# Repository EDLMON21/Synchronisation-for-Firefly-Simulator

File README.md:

## 🔥 Project Overview – *Synchronization for Firefly Simulator*  
### 🧠 Team Number: MON-21

👥 **Team Members:**  
- Mohammad Sami  
- Shivam Panwar  
- Gogineni Venkat Sumanth  
- Juluva Yashwanth  
- Lokesh  

---

### 📌 Problem Statement & Solution

Synchronization is a fundamental phenomenon in complex systems 🌐. To study it in real-time with flexibility, we need a programmable system with tunable parameters.

🧾 **Limitations of Old Designs:**  
The classical 1993 electronic fireflies lacked programmability and flexibility.  

⚙️ **Modern Solution:**  
Thanks to advancements in microcontrollers, we now have digital control and customizable experimentation possibilities.

---

### 🔧 Prototyping Journey

**🧩 Initial Prototype:**  
We designed a basic STM32 board with just the microcontroller to gain hands-on experience with PCB design using **STM32G030K8T6**.

**🔁 Second Iteration:**  
Integrated IR LEDs, photodiodes, and supporting components onto the board. Fabricated 2-3 units to test functionality, sync accuracy & design refinements.

**✅ Final Prototype:**  
After validation, we manufactured **9 boards (3×3 matrix)** for full-scale synchronization testing.

💻 Throughout, software development and debugging ran parallel to hardware iterations for smooth integration.

🧑‍🏫 The **STM32G030X** was suggested by our professor due to its suitability.  
🔦 The IR LED & photodiode combo was chosen for ambient light resistance and reliability in synchronization.

---

### ⚙️ Component Choices

- **🔲 STM32G030K8T6**  
  → Chosen from STM32G030 series (as fixed by prof) due to sufficient specs, easy soldering & availability.

- **🔦 IR LED & Phototransistor Pair**  
  → *SFH 4550 & SFH 309 FA*  
  → IR avoids visible light interference. The photodiode has peak sensitivity near **850nm** (matching our IR LED) and a narrow FOV for accurate detection.

- **🧰 Other Components**  
  → Transistors, LDO, micro USB connectors – sourced from WEL stock.

---

### 🚀 Running the Application

1. **🎯 Microcontroller:**  
   - STM32G030K8T6 or STM32G030K6T6  

2. **🛠 IDE:**  
   - STM32CubeIDE  

3. **📥 Compilation & Upload Steps:**  
   - Install **STM32CubeIDE**  
   - Download the `final.ioc` file from the **STM32G030K8T6** folder inside `src`  
   - Load `.ioc` file in your IDE  
   - Save the file to auto-generate code  
   - Replace the generated `main.c` with the `main.c` from the same folder  
   - Build the project 🏗️  
   - Flash the code using **StLink V2** (or equivalent)  
   - 🎉 Synchronization begins once phototransistors start detecting LED flashes!

---

Final Product

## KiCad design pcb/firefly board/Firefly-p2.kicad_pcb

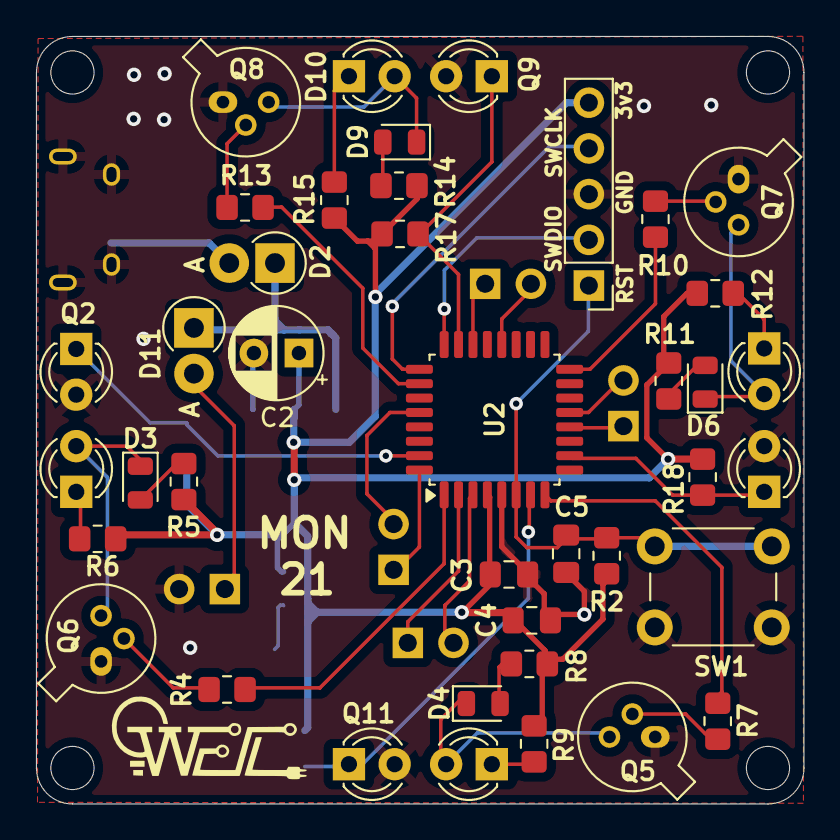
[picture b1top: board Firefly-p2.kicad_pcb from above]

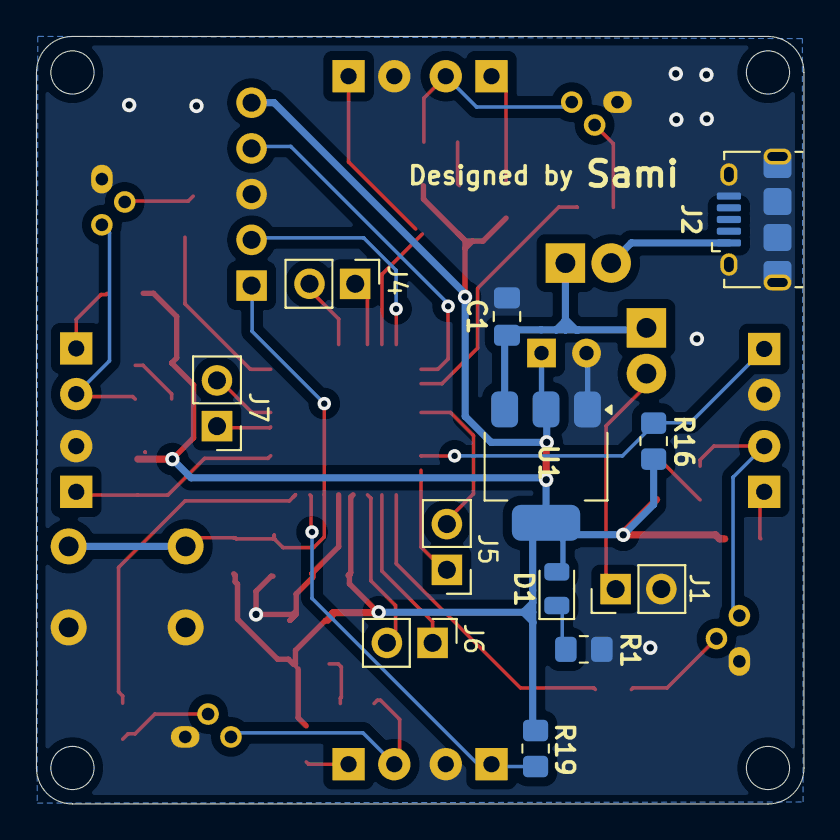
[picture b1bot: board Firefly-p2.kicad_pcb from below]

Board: 2 copper layers, 42.6 x 42.6 mm, 52 parts (12 on the bottom side), 41 nets.

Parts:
C1: 22u; C_0805_2012Metric_Pad1.18x1.45mm_HandSolder
C2: 22uF; CP_Radial_D5.0mm_P2.50mm
C3: 100nF; C_0805_2012Metric_Pad1.18x1.45mm_HandSolder
C4: 10uF; C_0805_2012Metric_Pad1.18x1.45mm_HandSolder
C5: 100n; C_0805_2012Metric_Pad1.18x1.45mm_HandSolder
D1, D3, D4, D6, D9: LED; LED_0805_2012Metric
D2, D11: D_Schottky; D_DO-41_SOD81_P2.54mm_Vertical_AnodeUp
D5, D7, D8, D10: SFH_4550; LED_D3.0mm_Clear
J1: Power_line; PinHeader_1x02_P2.54mm_Vertical
J2: USB_B_Micro; USB_Micro-B_Amphenol_10118194-0001LF_Horizontal
J3: Conn_01x05_Socket; PinHeader_1x05_P2.54mm_Vertical
J4: line_2; PinHeader_1x02_P2.54mm_Vertical
J5: line_3; PinHeader_1x02_P2.54mm_Vertical
J6: line_4; PinHeader_1x02_P2.54mm_Vertical
J7: line_1; PinHeader_1x02_P2.54mm_Vertical
Q2, Q9, Q10, Q11: SFH309; LED_D3.0mm_Clear
Q5, Q6, Q7, Q8: 2N2222; TO-18-3
R1, R4, R7, R10, R13: 1k; R_0805_2012Metric_Pad1.20x1.40mm_HandSolder
R2, R16, R17, R18, R19: 10k; R_0805_2012Metric_Pad1.20x1.40mm_HandSolder
R5, R8, R11, R14: 100r; R_0805_2012Metric_Pad1.20x1.40mm_HandSolder
R6, R9, R12, R15: 330r; R_0805_2012Metric_Pad1.20x1.40mm_HandSolder
SW1: SW_Push; SW_PUSH_6mm
U1: AMS1117-3.3; SOT-223-3_TabPin2
U2: STM32G030K8Tx; LQFP-32_7x7mm_P0.8mm

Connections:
+3.3V: C2.1, C3.1, C4.1, D1.2 (A), J3.5, R2.2, R5.1, R6.1, R8.1, R9.1, R11.1, R12.1, R14.1, R15.1, R16.2, R17.2, R18.2, R19.2, U1.2 (VO), U2.4 (VDD)
/PA0: Q11.1 (C), R19.1, U2.7 (PA0)
/PA1: R7.2, U2.8 (PA1)
/PA3: Q10.1 (C), R18.1, U2.10 (PA3)
/PA5: J7.1, U2.12 (PA5)
/PA6: J7.2, U2.13 (PA6)
/PA11: J4.1, U2.22 (PA9/PA11)
/PA12: Q9.1 (C), R17.1, U2.23 (PA10/PA12)
/PA15: R13.2, U2.26 (PA15)
/PB1: R10.2, U2.16 (PB1)
/PB4: J5.2, U2.28 (PB4)
/PB7: Q2.1 (C), R16.1, U2.31 (PB7)
/PB8: J5.1, U2.32 (PB8)
/PB9: R4.2, U2.1 (PB9)
/PC6: J4.2, U2.20 (PC6)
/PC14: J6.1, U2.2 (PC14)
/PC15: J6.2, U2.3 (PC15)
/RST: C5.1, J3.1, R2.1, SW1.2, U2.6 (NRST)
/SWCLK: J3.4, U2.25 (PA14)
/SWDIO: J3.2, U2.24 (PA13)
GND: C1.2, C2.2, C3.2, C4.2, C5.2, J1.2, J2.5 (GND), J2.6 (Shield), J3.3, Q2.2 (E), Q5.1 (E), Q6.1 (E), Q7.1 (E), Q8.1 (E), Q9.2 (E), Q10.2 (E), Q11.2 (E), R1.2, SW1.1, U1.1 (GND), U2.5 (VSS)
unnamed: D1.1 (K), R1.1
unnamed: D2.2 (A), J2.1 (VBUS)
unnamed: D3.2 (A), R5.2
unnamed: D3.1 (K), D5.2, Q6.3 (C)
unnamed: D4.2 (A), R8.2
unnamed: D4.1 (K), D8.2, Q5.3 (C)
unnamed: D5.1, R6.2
unnamed: D6.2 (A), R11.2
unnamed: D6.1 (K), D7.2, Q7.3 (C)
unnamed: D7.1, R12.2
unnamed: D8.1, R9.2
unnamed: D9.2 (A), R14.2
unnamed: D9.1 (K), D10.2, Q8.3 (C)
unnamed: D10.1, R15.2
unnamed: D11.2 (A), J1.1
unnamed: Q5.2 (B), R7.1
unnamed: Q6.2 (B), R4.1
unnamed: Q7.2 (B), R10.1
unnamed: Q8.2 (B), R13.1
VBUS: C1.1, D2.1 (K), D11.1 (K), U1.3 (VI)

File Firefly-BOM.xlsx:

Name | Qty | Value | Footprint | Type | Supplier | Cost (Rs.)
Capacitor | 1 | 22uF | Capacitor_SMD:C_0805_2012Metric_Pad1.18x1.45mm_HandSolder | Consumable | WEL | NA
Tantalum Capacitor | 1 | 22uF | Capacitor_THT:CP_Radial_D4.0mm_P1.50mm | Consumable | Robu (https://robu.in/product/22uf-16v-tantalum-capacitor-dip-pack-of-5/) | 99/-
Capacitor | 2 | 100nF | Capacitor_SMD:C_0805_2012Metric_Pad1.18x1.45mm_HandSolder | Consumable | WEL | NA
Capacitor | 1 | 10uF | Capacitor_SMD:C_0805_2012Metric_Pad1.18x1.45mm_HandSolder | Consumable | WEL | NA
LEDs | 5 | LED | LED_SMD:LED_0805_2012Metric | Consumable | WEL | NA
Schottky Diode | 2 | D_Schottky | Diode_THT:D_DO-41_SOD81_P2.54mm_Vertical_AnodeUp | Consumable | Robu (https://robu.in/product/1n5817-multicomp-pro-1n5817-schottky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 | 9/-
IR Led | 4 | SFH_4550 | LED_THT:LED_D3.0mm_Clear | Consumable | RS Deliveries (https://in.rsdelivers.com/en/product/ams-osram/sfh-4550/sfh-4550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 | 46/-
Pin Header | 1 | Power_line | Connector_PinHeader_2.54mm:PinHeader_1x02_P2.54mm_Vertical | Consumable | WEL | NA
Micro USB Receptor | 1 | USB_B_Micro | Connector_USB:USB_Micro-B_Amphenol_10118194-0001LF_Horizontal | Consumable | WEL | NA
Pin Header | 1 | Conn_01x05_Socket | Connector_PinHeader_2.54mm:PinHeader_1x05_P2.54mm_Vertical | Consumable | WEL | NA
Pin Header | 1 | line_2 | Connector_PinHeader_2.54mm:PinHeader_1x02_P2.54mm_Vertical | Consumable | WEL | NA
Pin Header | 1 | line_3 | Connector_PinHeader_2.54mm:PinHeader_1x02_P2.54mm_Vertical | Consumable | WEL | NA
Pin Header | 1 | line_4 | Connector_PinHeader_2.54mm:PinHeader_1x02_P2.54mm_Vertical | Consumable | WEL | NA
Pin Header | 1 | line_1 | Connector_PinHeader_2.54mm:PinHeader_1x02_P2.54mm_Vertical | Consumable | WEL | NA
PhotoTransistor | 4 | SFH309 | LED_THT:LED_D3.0mm_Clear | Consumable | RS Deliveries (https://in.rsdelivers.com/bh/product/ams-osram/sfh-309-fa/sfh-30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 | 28/-
NPN BJT | 4 | 2N2222 | Package_TO_SOT_THT:TO-18-3 | Consumable | WEL | NA
Resistor | 9 | 120r | Resistor_SMD:R_0805_2012Metric_Pad1.20x1.40mm_HandSolder | Consumable | WEL | NA
Resistor | 1 | 10k | Resistor_SMD:R_0805_2012Metric_Pad1.20x1.40mm_HandSolder | Consumable | WEL | NA
Resistor | 4 | 330r | Resistor_SMD:R_0805_2012Metric_Pad1.20x1.40mm_HandSolder | Consumable | WEL | NA
Resistor | 4 | 50k | Resistor_SMD:R_0805_2012Metric_Pad1.20x1.40mm_HandSolder | Consumable | WEL | NA
Push Button | 1 | SW_Push | Button_Switch_THT:SW_PUSH_6mm | Consumable | WEL | NA
LDO | 1 | AMS1117-3.3 | Package_TO_SOT_SMD:SOT-223-3_TabPin2 | Consumable | WEL | NA
MCU | 1 | STM32G030K8Tx | Package_QFP:LQFP-32_7x7mm_P0.8mm | IC | Robu (https://robu.in/product/stm32g030k8t6-stmicroelectronics-stm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 | 129/-

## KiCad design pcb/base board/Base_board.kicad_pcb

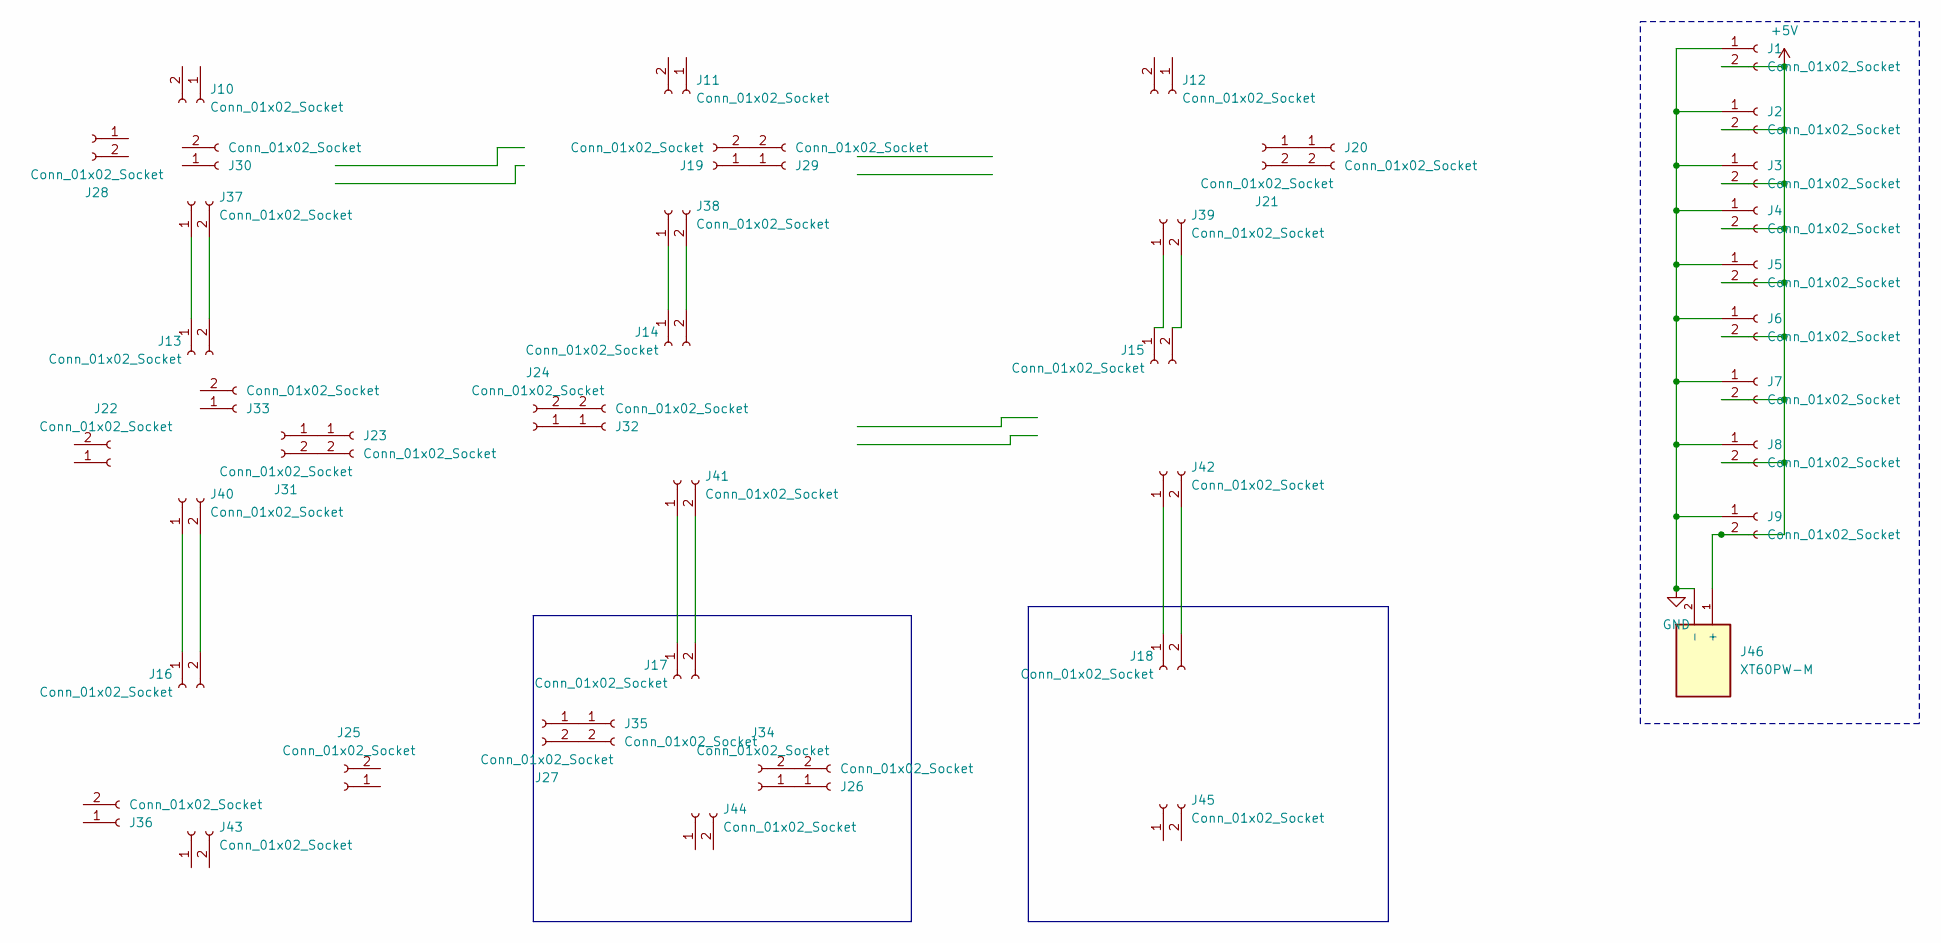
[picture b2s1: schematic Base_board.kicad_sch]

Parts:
J1, J2, J3, J4, J5, J6, J7, J8, J9, J10, J11, J12, J13, J14, J15, J16, J17, J18, J19, J20, J21, J22, J23, J24, J25, J26, J27, J28, J29, J30, J31, J32, J33, J34, J35, J36, J37, J38, J39, J40, J41, J42, J43, J44, J45: Conn_01x02_Socket; PinSocket_1x02_P2.54mm_Vertical
J46: XT60PW-M; AMASS_XT60PW-M; PARTREV V1.2

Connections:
+5V: J1.2, J2.2, J3.2, J4.2, J5.2, J6.2, J7.2, J8.2, J9.2, J46.1 (+)
GND: J1.1, J2.1, J3.1, J4.1, J5.1, J6.1, J7.1, J8.1, J9.1, J46.2 (-)
unnamed: J13.1, J37.1
unnamed: J13.2, J37.2
unnamed: J14.1, J38.1
unnamed: J14.2, J38.2
unnamed: J15.1, J39.1
unnamed: J15.2, J39.2
unnamed: J16.1, J40.1
unnamed: J16.2, J40.2
unnamed: J17.1, J41.1
unnamed: J17.2, J41.2
unnamed: J18.1, J42.1
unnamed: J18.2, J42.2
unnamed: J19.1, J29.1
unnamed: J19.2, J29.2
unnamed: J20.1, J21.1
unnamed: J20.2, J21.2
unnamed: J23.1, J31.1
unnamed: J23.2, J31.2
unnamed: J24.1, J32.1
unnamed: J24.2, J32.2
unnamed: J26.1, J34.1
unnamed: J26.2, J34.2
unnamed: J27.1, J35.1
unnamed: J27.2, J35.2

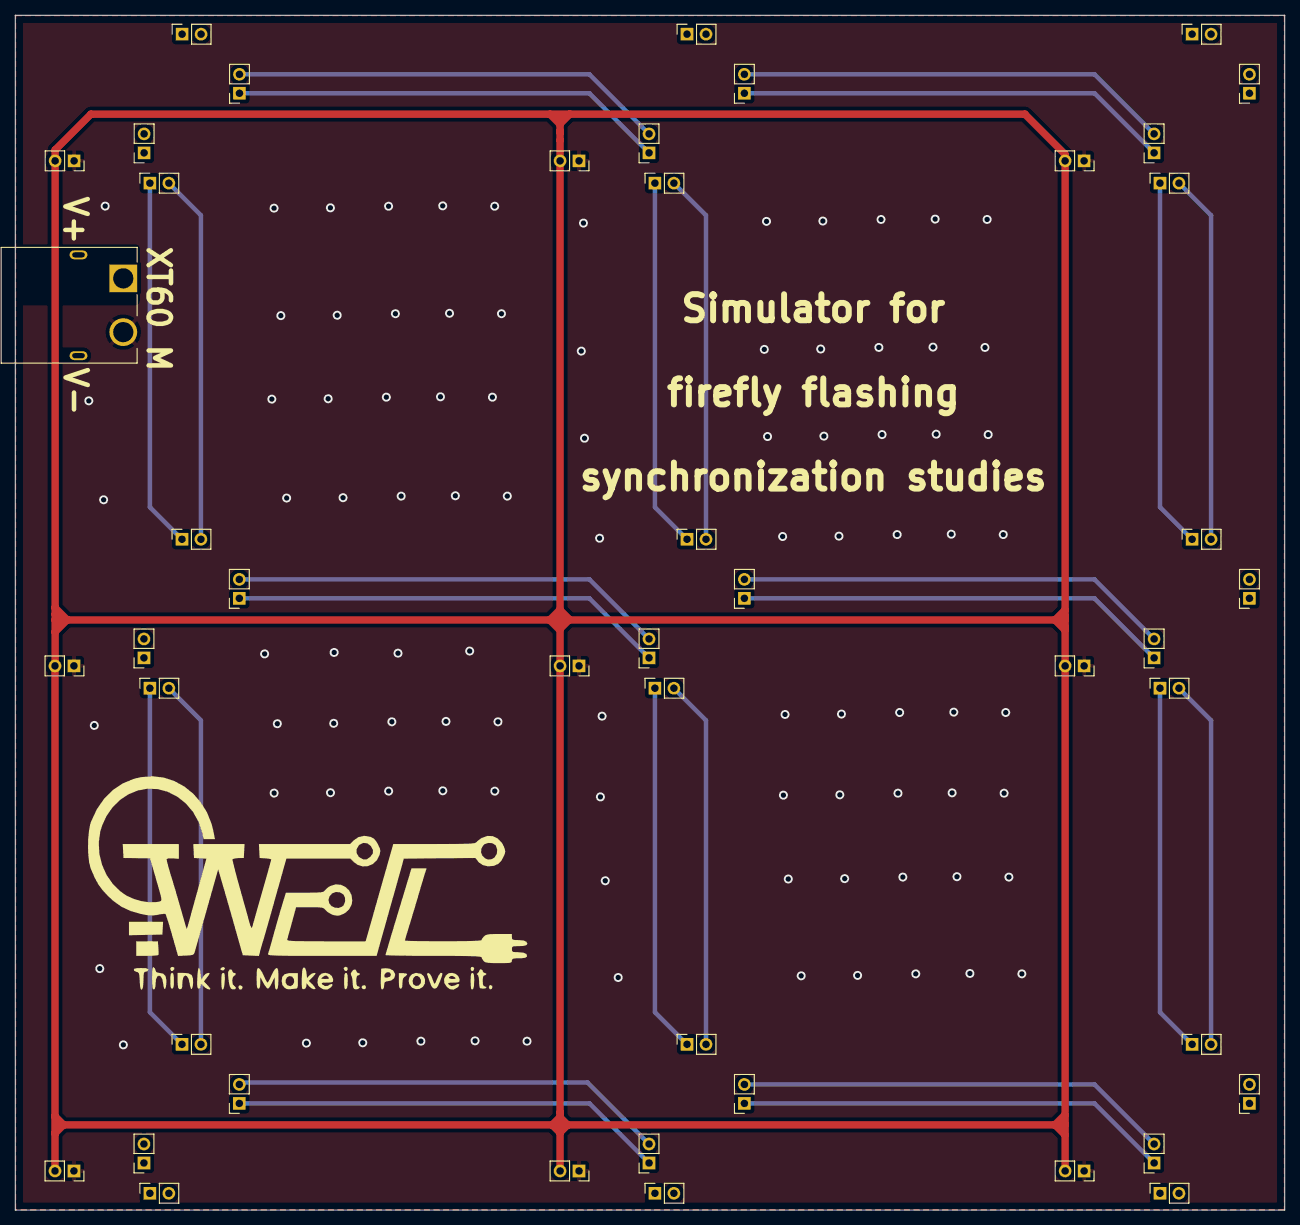
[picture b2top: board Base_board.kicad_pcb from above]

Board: 2 copper layers, 170.0 x 160.0 mm, 46 parts (0 on the bottom side), 26 nets.

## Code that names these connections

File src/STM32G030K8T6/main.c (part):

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  HAL_ADC_Init(&hadc1);

  /* Configure for the selected ADC regular channel */
  sConfig.Channel = ADC_CHANNEL_0;  /* PA0 */
  sConfig.Rank = ADC_REGULAR_RANK_1;
  sConfig.SamplingTime = ADC_SAMPLINGTIME_COMMON_1;
  HAL_ADC_ConfigChannel(&hadc1, &sConfig);

  sConfig.Channel = ADC_CHANNEL_3;  /* PA3 */
  sConfig.Rank = ADC_REGULAR_RANK_2;
  HAL_ADC_ConfigChannel(&hadc1, &sConfig);

  sConfig.Channel = ADC_CHANNEL_16; /* PA12 */
  sConfig.Rank = ADC_REGULAR_RANK_3;
  HAL_ADC_ConfigChannel(&hadc1, &sConfig);

  sConfig.Channel = ADC_CHANNEL_11; /* PB7 */
  sConfig.Rank = ADC_REGULAR_RANK_4;
  HAL_ADC_ConfigChannel(&hadc1, &sConfig);
}
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  /*Configure GPIO pin Output Level */
  HAL_GPIO_WritePin(GPIOA, GPIO_PIN_1|GPIO_PIN_15, GPIO_PIN_RESET);

  /*Configure GPIO pins : PB9 PB1 */
  GPIO_InitStruct.Pin = GPIO_PIN_9|GPIO_PIN_1;
  GPIO_InitStruct.Mode = GPIO_MODE_OUTPUT_PP;
  GPIO_InitStruct.Pull = GPIO_NOPULL;
  GPIO_InitStruct.Speed = GPIO_SPEED_FREQ_LOW;
  HAL_GPIO_Init(GPIOB, &GPIO_InitStruct);

  /*Configure GPIO pins : PA1 PA15 */
  GPIO_InitStruct.Pin = GPIO_PIN_1|GPIO_PIN_15;
  GPIO_InitStruct.Mode = GPIO_MODE_OUTPUT_PP;
  GPIO_InitStruct.Pull = GPIO_NOPULL;
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
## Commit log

2025-04-13 second commit :)
2025-04-13 other images

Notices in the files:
src/STM32G030K8T6/main.c:
Copyright (c) 2025 STMicroelectronics.
All rights reserved.
This software is licensed under terms that can be found in the LICENSE file
